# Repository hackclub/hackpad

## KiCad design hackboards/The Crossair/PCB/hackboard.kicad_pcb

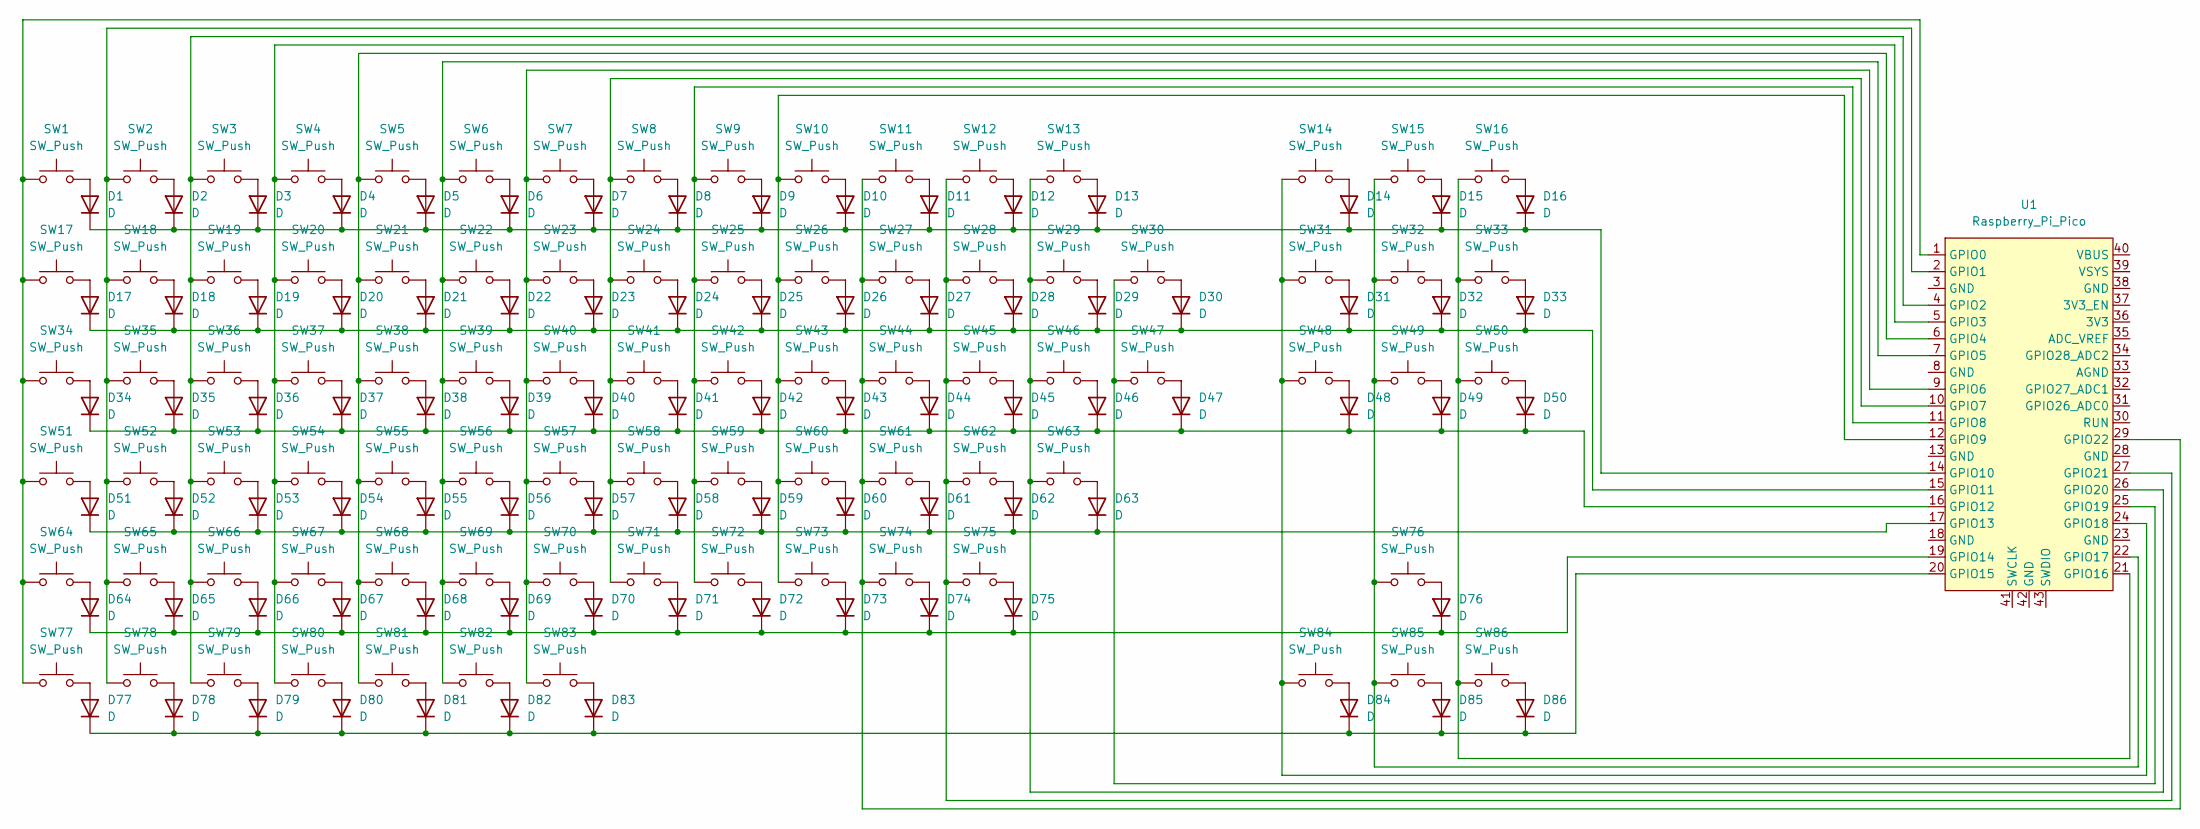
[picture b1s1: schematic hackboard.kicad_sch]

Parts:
D1, D2, D3, D4, D5, D6, D7, D8, D9, D10, D11, D12, D13, D14, D15, D16, D17, D18, D19, D20, D21, D22, D23, D24, D25, D26, D27, D28, D29, D30, D31, D32, D33, D34, D35, D36, D37, D38, D39, D40, D41, D42, D43, D44, D45, D46, D47, D48, D49, D50, D51, D52, D53, D54, D55, D56, D57, D58, D59, D60, D61, D62, D63, D64, D65, D66, D67, D68, D69, D70, D71, D72, D73, D74, D75, D76, D77, D78, D79, D80, D81, D82, D83, D84, D85, D86: D; D_DO-35_SOD27_P7.62mm_Horizontal
SW1, SW2, SW3, SW4, SW5, SW6, SW7, SW8, SW9, SW10, SW11, SW12, SW13, SW14, SW15, SW16, SW17, SW18, SW19, SW20, SW21, SW22, SW23, SW24, SW25, SW26, SW27, SW28, SW29, SW31, SW32, SW33, SW35, SW36, SW37, SW38, SW39, SW40, SW41, SW42, SW43, SW44, SW45, SW46, SW48, SW49, SW50, SW52, SW53, SW54, SW55, SW56, SW57, SW58, SW59, SW60, SW61, SW62, SW65, SW66, SW67, SW68, SW69, SW70, SW71, SW72, SW73, SW74, SW76, SW84, SW85, SW86: SW_Push; SW_Cherry_MX_1.00u_PCB
SW30: SW_Push; SW_Cherry_MX_2.00u_PCB
SW34, SW47, SW77, SW79, SW81, SW82, SW83: SW_Push; SW_Cherry_MX_1.50u_PCB
SW51: SW_Push; SW_Cherry_MX_1.75u_PCB
SW63, SW64: SW_Push; SW_Cherry_MX_2.25u_PCB
SW75: SW_Push; SW_Cherry_MX_2.75u_PCB
SW78: SW_Push; SW_Cherry_MX_1.25u_PCB
SW80: SW_Push; SW_Cherry_MX_6.25u_PCB
U1: Raspberry_Pi_Pico

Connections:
unnamed: D1.2 (A), SW1.2
unnamed: D1.1 (K), D2.1 (K), D3.1 (K), D4.1 (K), D5.1 (K), D6.1 (K), D7.1 (K), D8.1 (K), D9.1 (K), D10.1 (K), D11.1 (K), D12.1 (K), D13.1 (K), D14.1 (K), D15.1 (K), D16.1 (K), U1.14 (GPIO10)
unnamed: D2.2 (A), SW2.2
unnamed: D3.2 (A), SW3.2
unnamed: D4.2 (A), SW4.2
unnamed: D5.2 (A), SW5.2
unnamed: D6.2 (A), SW6.2
unnamed: D7.2 (A), SW7.2
unnamed: D8.2 (A), SW8.2
unnamed: D9.2 (A), SW9.2
unnamed: D10.2 (A), SW10.2
unnamed: D11.2 (A), SW11.2
unnamed: D12.2 (A), SW12.2
unnamed: D13.2 (A), SW13.2
unnamed: D14.2 (A), SW14.2
unnamed: D15.2 (A), SW15.2
unnamed: D16.2 (A), SW16.2
unnamed: D17.2 (A), SW17.2
unnamed: D17.1 (K), D18.1 (K), D19.1 (K), D20.1 (K), D21.1 (K), D22.1 (K), D23.1 (K), D24.1 (K), D25.1 (K), D26.1 (K), D27.1 (K), D28.1 (K), D29.1 (K), D30.1 (K), D31.1 (K), D32.1 (K), D33.1 (K), U1.15 (GPIO11)
unnamed: D18.2 (A), SW18.2
unnamed: D19.2 (A), SW19.2
unnamed: D20.2 (A), SW20.2
unnamed: D21.2 (A), SW21.2
unnamed: D22.2 (A), SW22.2
unnamed: D23.2 (A), SW23.2
unnamed: D24.2 (A), SW24.2
unnamed: D25.2 (A), SW25.2
unnamed: D26.2 (A), SW26.2
unnamed: D27.2 (A), SW27.2
unnamed: D28.2 (A), SW28.2
unnamed: D29.2 (A), SW29.2
unnamed: D30.2 (A), SW30.2
unnamed: D31.2 (A), SW31.2
unnamed: D32.2 (A), SW32.2
unnamed: D33.2 (A), SW33.2
unnamed: D34.2 (A), SW34.2
unnamed: D34.1 (K), D35.1 (K), D36.1 (K), D37.1 (K), D38.1 (K), D39.1 (K), D40.1 (K), D41.1 (K), D42.1 (K), D43.1 (K), D44.1 (K), D45.1 (K), D46.1 (K), D47.1 (K), D48.1 (K), D49.1 (K), D50.1 (K), U1.16 (GPIO12)
unnamed: D35.2 (A), SW35.2
unnamed: D36.2 (A), SW36.2
unnamed: D37.2 (A), SW37.2
unnamed: D38.2 (A), SW38.2
unnamed: D39.2 (A), SW39.2
unnamed: D40.2 (A), SW40.2
unnamed: D41.2 (A), SW41.2
unnamed: D42.2 (A), SW42.2
unnamed: D43.2 (A), SW43.2
unnamed: D44.2 (A), SW44.2
unnamed: D45.2 (A), SW45.2
unnamed: D46.2 (A), SW46.2
unnamed: D47.2 (A), SW47.2
unnamed: D48.2 (A), SW48.2
unnamed: D49.2 (A), SW49.2
unnamed: D50.2 (A), SW50.2
unnamed: D51.2 (A), SW51.2
unnamed: D51.1 (K), D52.1 (K), D53.1 (K), D54.1 (K), D55.1 (K), D56.1 (K), D57.1 (K), D58.1 (K), D59.1 (K), D60.1 (K), D61.1 (K), D62.1 (K), D63.1 (K), U1.17 (GPIO13)
unnamed: D52.2 (A), SW52.2
unnamed: D53.2 (A), SW53.2
unnamed: D54.2 (A), SW54.2
unnamed: D55.2 (A), SW55.2
unnamed: D56.2 (A), SW56.2
unnamed: D57.2 (A), SW57.2
unnamed: D58.2 (A), SW58.2
unnamed: D59.2 (A), SW59.2
unnamed: D60.2 (A), SW60.2
unnamed: D61.2 (A), SW61.2
unnamed: D62.2 (A), SW62.2
unnamed: D63.2 (A), SW63.2
unnamed: D64.2 (A), SW64.2
unnamed: D64.1 (K), D65.1 (K), D66.1 (K), D67.1 (K), D68.1 (K), D69.1 (K), D70.1 (K), D71.1 (K), D72.1 (K), D73.1 (K), D74.1 (K), D75.1 (K), D76.1 (K), U1.19 (GPIO14)
unnamed: D65.2 (A), SW65.2
unnamed: D66.2 (A), SW66.2
unnamed: D67.2 (A), SW67.2
unnamed: D68.2 (A), SW68.2
unnamed: D69.2 (A), SW69.2
unnamed: D70.2 (A), SW70.2
unnamed: D71.2 (A), SW71.2
unnamed: D72.2 (A), SW72.2
unnamed: D73.2 (A), SW73.2
unnamed: D74.2 (A), SW74.2
unnamed: D75.2 (A), SW75.2
unnamed: D76.2 (A), SW76.2
unnamed: D77.2 (A), SW77.2
unnamed: D77.1 (K), D78.1 (K), D79.1 (K), D80.1 (K), D81.1 (K), D82.1 (K), D83.1 (K), D84.1 (K), D85.1 (K), D86.1 (K), U1.20 (GPIO15)
unnamed: D78.2 (A), SW78.2
unnamed: D79.2 (A), SW79.2
unnamed: D80.2 (A), SW80.2
unnamed: D81.2 (A), SW81.2
unnamed: D82.2 (A), SW82.2
unnamed: D83.2 (A), SW83.2
unnamed: D84.2 (A), SW84.2
unnamed: D85.2 (A), SW85.2
unnamed: D86.2 (A), SW86.2
unnamed: SW1.1, SW17.1, SW34.1, SW51.1, SW64.1, SW77.1, U1.1 (GPIO0)
unnamed: SW2.1, SW18.1, SW35.1, SW52.1, SW65.1, SW78.1, U1.2 (GPIO1)
unnamed: SW3.1, SW19.1, SW36.1, SW53.1, SW66.1, SW79.1, U1.4 (GPIO2)
unnamed: SW4.1, SW20.1, SW37.1, SW54.1, SW67.1, SW80.1, U1.5 (GPIO3)
unnamed: SW5.1, SW21.1, SW38.1, SW55.1, SW68.1, SW81.1, U1.6 (GPIO4)
unnamed: SW6.1, SW22.1, SW39.1, SW56.1, SW69.1, SW82.1, U1.7 (GPIO5)
unnamed: SW7.1, SW23.1, SW40.1, SW57.1, SW70.1, SW83.1, U1.9 (GPIO6)
unnamed: SW8.1, SW24.1, SW41.1, SW58.1, SW71.1, U1.10 (GPIO7)
unnamed: SW9.1, SW25.1, SW42.1, SW59.1, SW72.1, U1.11 (GPIO8)
unnamed: SW10.1, SW26.1, SW43.1, SW60.1, SW73.1, U1.12 (GPIO9)
unnamed: SW16.1, SW33.1, SW50.1, SW86.1, U1.21 (GPIO16)
unnamed: SW15.1, SW32.1, SW49.1, SW76.1, SW85.1, U1.22 (GPIO17)
unnamed: SW14.1, SW31.1, SW48.1, SW84.1, U1.24 (GPIO18)
unnamed: SW30.1, SW47.1, U1.25 (GPIO19)
unnamed: SW13.1, SW29.1, SW46.1, SW63.1, U1.26 (GPIO20)
unnamed: SW12.1, SW28.1, SW45.1, SW62.1, SW75.1, U1.27 (GPIO21)
unnamed: SW11.1, SW27.1, SW44.1, SW61.1, SW74.1, U1.29 (GPIO22)

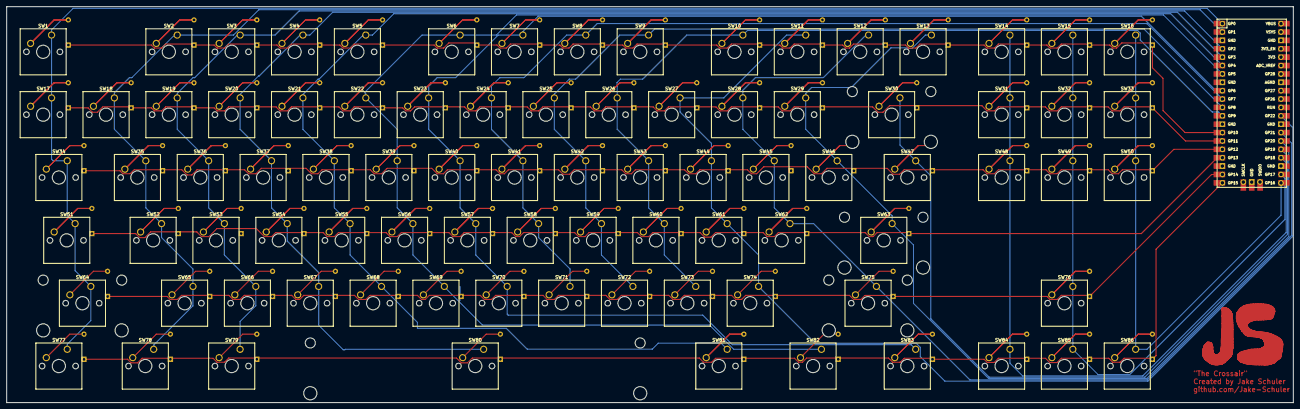
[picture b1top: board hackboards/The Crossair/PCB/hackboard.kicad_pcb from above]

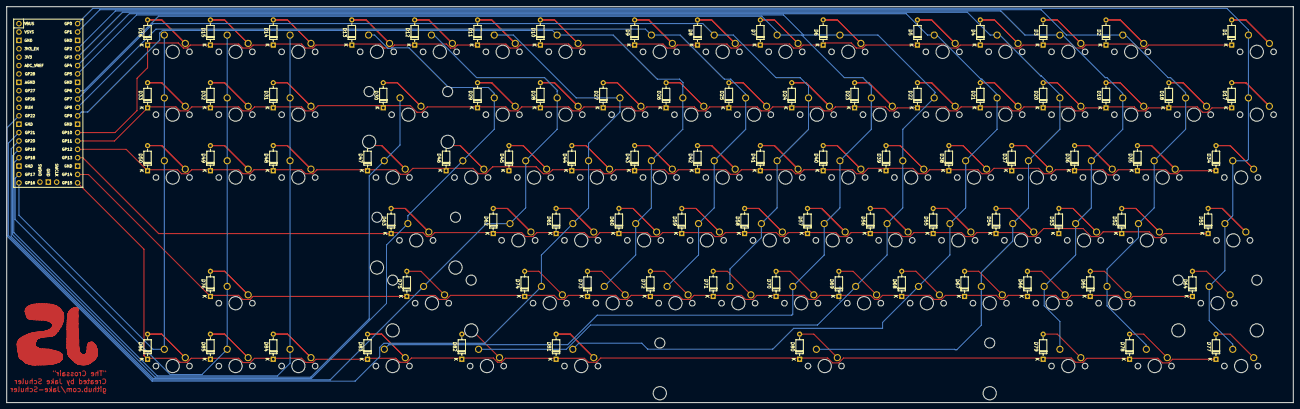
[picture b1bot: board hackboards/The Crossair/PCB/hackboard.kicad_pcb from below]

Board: 2 copper layers, 390.0 x 120.0 mm, 173 parts (86 on the bottom side), 109 nets.

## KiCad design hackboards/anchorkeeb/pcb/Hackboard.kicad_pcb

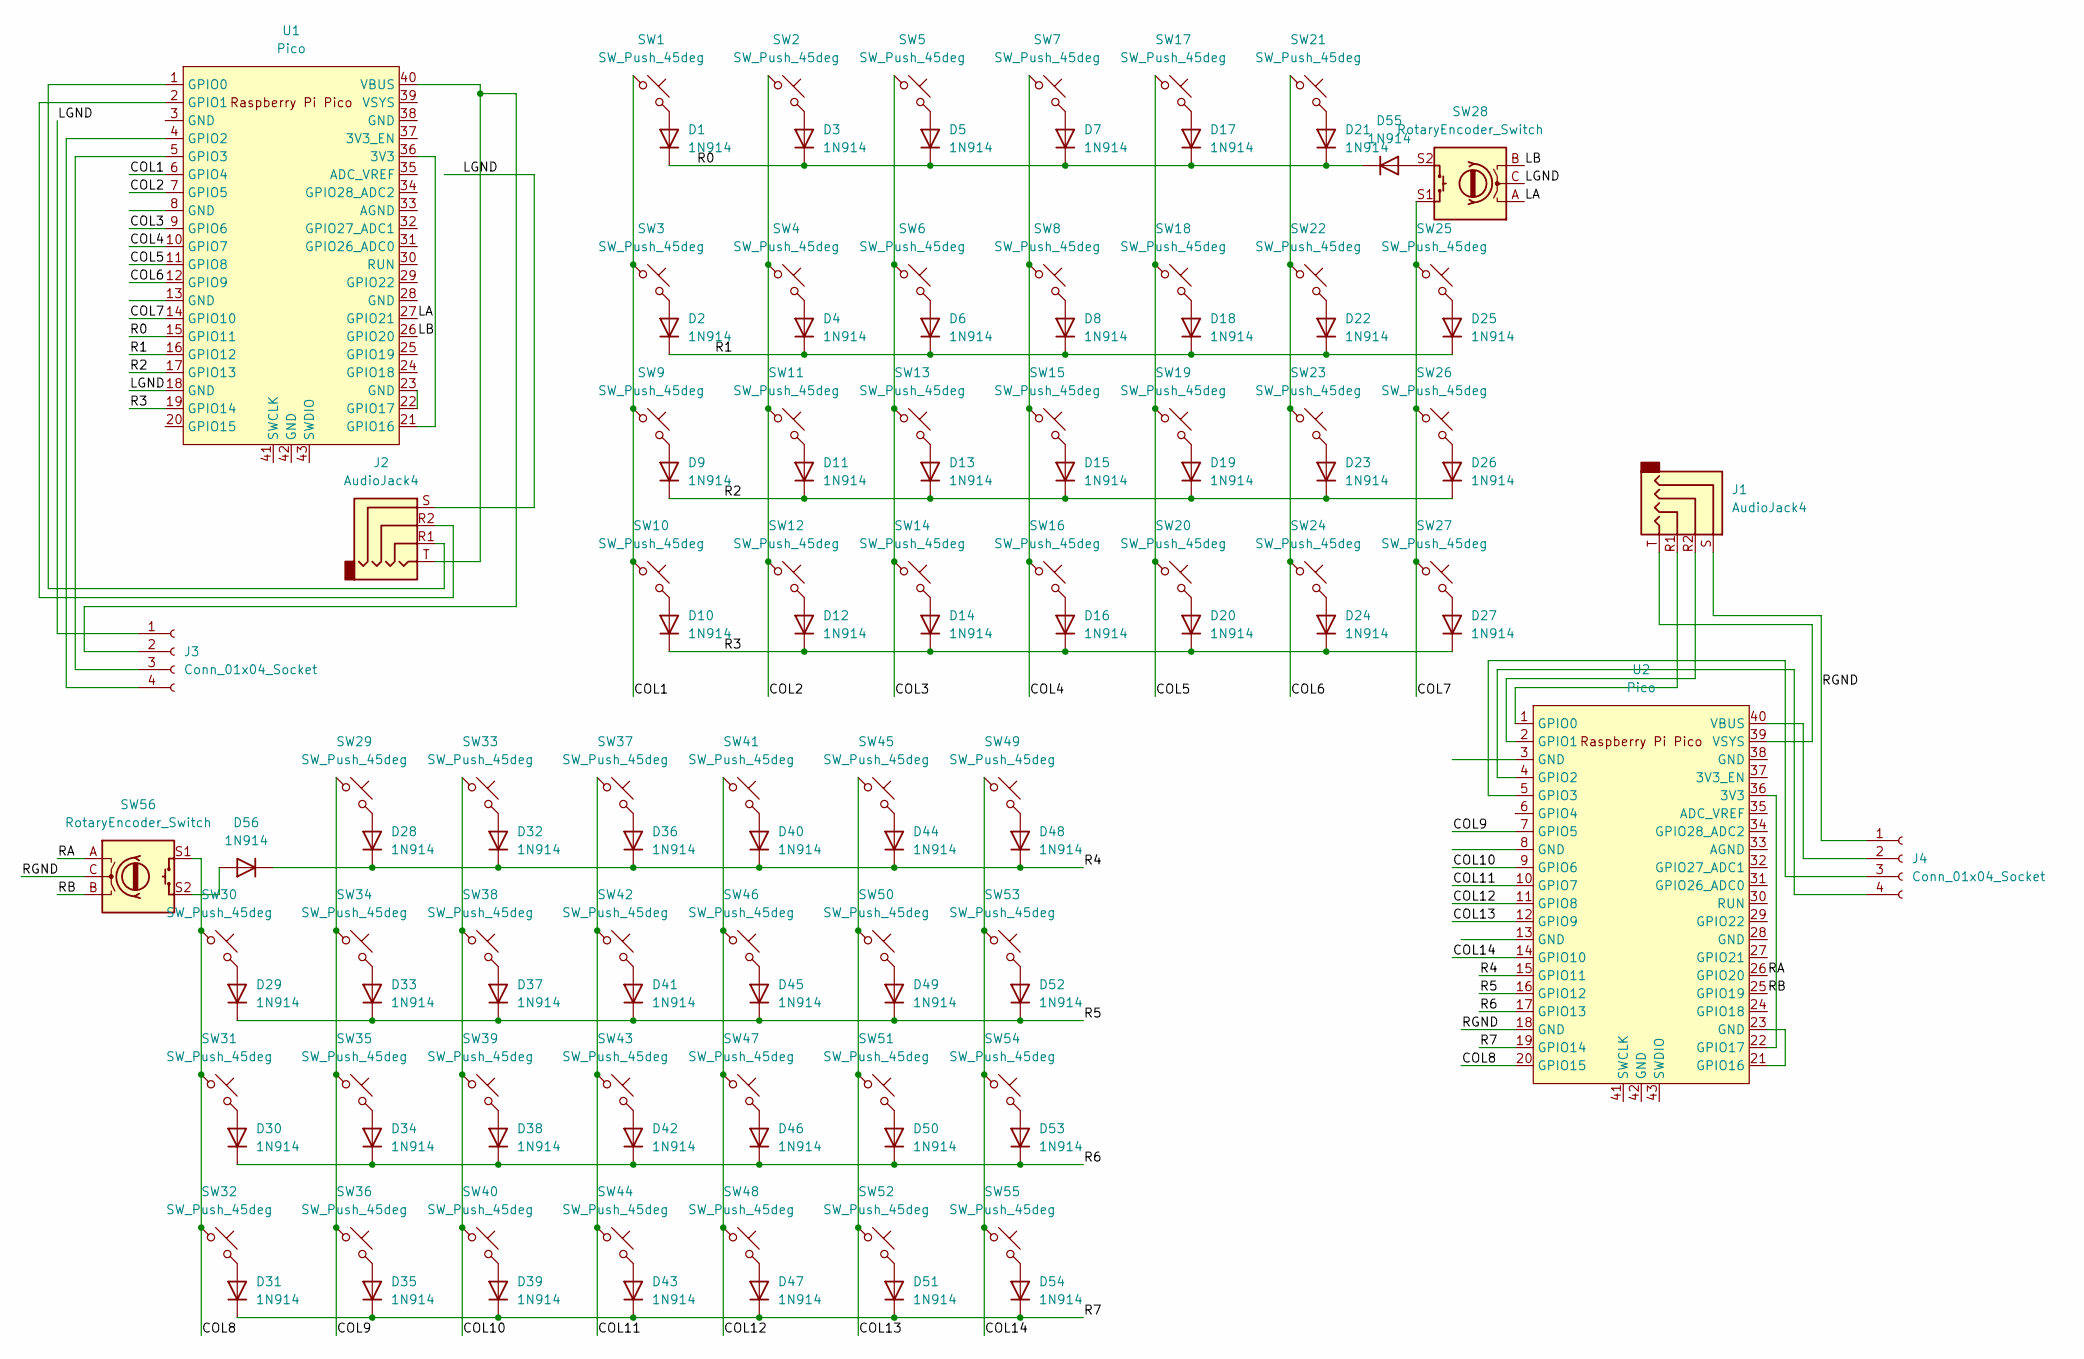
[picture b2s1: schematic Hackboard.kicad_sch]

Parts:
D1, D2, D3, D4, D5, D6, D7, D8, D9, D10, D11, D12, D13, D14, D15, D16, D17, D18, D19, D20, D21, D22, D23, D24, D25, D26, D27, D28, D29, D30, D31, D32, D33, D34, D35, D36, D37, D38, D39, D40, D41, D42, D43, D44, D45, D46, D47, D48, D49, D50, D51, D52, D53, D54, D55, D56: 1N914; D_DO-35_SOD27_P7.62mm_Horizontal
J1, J2: AudioJack4; Jack_3.5mm_PJ320D_Horizontal
J3, J4: Conn_01x04_Socket; SSD1306-0.91-OLED-4pin-128x32
SW1, SW2, SW3, SW4, SW5, SW6, SW7, SW8, SW9, SW10, SW11, SW12, SW13, SW14, SW15, SW16, SW17, SW18, SW19, SW20, SW21, SW22, SW23, SW24, SW25, SW26, SW27, SW29, SW30, SW31, SW32, SW33, SW34, SW35, SW36, SW37, SW38, SW39, SW40, SW41, SW42, SW43, SW44, SW45, SW46, SW47, SW48, SW49, SW50, SW51, SW52, SW53, SW54, SW55: SW_Push_45deg; SW_Cherry_MX_1.00u_PCB
SW28, SW56: RotaryEncoder_Switch; RotaryEncoder_Alps_EC11E-Switch_Vertical_H20mm
U1, U2: Pico; RPi_Pico_SMD_TH

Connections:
/COL1: SW1.1, SW3.1, SW9.1, SW10.1, U1.6 (GPIO4)
/COL2: SW2.1, SW4.1, SW11.1, SW12.1, U1.7 (GPIO5)
/COL3: SW5.1, SW6.1, SW13.1, SW14.1, U1.9 (GPIO6)
/COL4: SW7.1, SW8.1, SW15.1, SW16.1, U1.10 (GPIO7)
/COL5: SW17.1, SW18.1, SW19.1, SW20.1, U1.11 (GPIO8)
/COL6: SW21.1, SW22.1, SW23.1, SW24.1, U1.12 (GPIO9)
/COL7: SW25.1, SW26.1, SW27.1, SW28.S1, U1.14 (GPIO10)
/COL8: SW30.1, SW31.1, SW32.1, SW56.S1, U2.20 (GPIO15)
/COL9: SW29.1, SW34.1, SW35.1, SW36.1, U2.7 (GPIO5)
/COL10: SW33.1, SW38.1, SW39.1, SW40.1, U2.9 (GPIO6)
/COL11: SW37.1, SW42.1, SW43.1, SW44.1, U2.10 (GPIO7)
/COL12: SW41.1, SW46.1, SW47.1, SW48.1, U2.11 (GPIO8)
/COL13: SW45.1, SW50.1, SW51.1, SW52.1, U2.12 (GPIO9)
/COL14: SW49.1, SW53.1, SW54.1, SW55.1, U2.14 (GPIO10)
/LA: SW28.A, U1.27 (GPIO21)
/LB: SW28.B, U1.26 (GPIO20)
/LGND: J2.S, J3.1, SW28.C, U1.18 (GND)
/R0: D1.1 (K), D3.1 (K), D5.1 (K), D7.1 (K), D17.1 (K), D21.1 (K), D55.1 (K), U1.15 (GPIO11)
/R1: D2.1 (K), D4.1 (K), D6.1 (K), D8.1 (K), D18.1 (K), D22.1 (K), D25.1 (K), U1.16 (GPIO12)
/R2: D9.1 (K), D11.1 (K), D13.1 (K), D15.1 (K), D19.1 (K), D23.1 (K), D26.1 (K), U1.17 (GPIO13)
/R3: D10.1 (K), D12.1 (K), D14.1 (K), D16.1 (K), D20.1 (K), D24.1 (K), D27.1 (K), U1.19 (GPIO14)
/R4: D28.1 (K), D32.1 (K), D36.1 (K), D40.1 (K), D44.1 (K), D48.1 (K), D56.1 (K), U2.15 (GPIO11)
/R5: D29.1 (K), D33.1 (K), D37.1 (K), D41.1 (K), D45.1 (K), D49.1 (K), D52.1 (K), U2.16 (GPIO12)
/R6: D30.1 (K), D34.1 (K), D38.1 (K), D42.1 (K), D46.1 (K), D50.1 (K), D53.1 (K), U2.17 (GPIO13)
/R7: D31.1 (K), D35.1 (K), D39.1 (K), D43.1 (K), D47.1 (K), D51.1 (K), D54.1 (K), U2.19 (GPIO14)
/RA: SW56.A, U2.26 (GPIO20)
/RB: SW56.B, U2.25 (GPIO19)
/RGND: J1.S, J4.1, SW56.C, U2.18 (GND)
unnamed: D1.2 (A), SW1.2
unnamed: D2.2 (A), SW3.2
unnamed: D3.2 (A), SW2.2
unnamed: D4.2 (A), SW4.2
unnamed: D5.2 (A), SW5.2
unnamed: D6.2 (A), SW6.2
unnamed: D7.2 (A), SW7.2
unnamed: D8.2 (A), SW8.2
unnamed: D9.2 (A), SW9.2
unnamed: D10.2 (A), SW10.2
unnamed: D11.2 (A), SW11.2
unnamed: D12.2 (A), SW12.2
unnamed: D13.2 (A), SW13.2
unnamed: D14.2 (A), SW14.2
unnamed: D15.2 (A), SW15.2
unnamed: D16.2 (A), SW16.2
unnamed: D17.2 (A), SW17.2
unnamed: D18.2 (A), SW18.2
unnamed: D19.2 (A), SW19.2
unnamed: D20.2 (A), SW20.2
unnamed: D21.2 (A), SW21.2
unnamed: D22.2 (A), SW22.2
unnamed: D23.2 (A), SW23.2
unnamed: D24.2 (A), SW24.2
unnamed: D25.2 (A), SW25.2
unnamed: D26.2 (A), SW26.2
unnamed: D27.2 (A), SW27.2
unnamed: D28.2 (A), SW29.2
unnamed: D29.2 (A), SW30.2
unnamed: D30.2 (A), SW31.2
unnamed: D31.2 (A), SW32.2
unnamed: D32.2 (A), SW33.2
unnamed: D33.2 (A), SW34.2
unnamed: D34.2 (A), SW35.2
unnamed: D35.2 (A), SW36.2
unnamed: D36.2 (A), SW37.2
unnamed: D37.2 (A), SW38.2
unnamed: D38.2 (A), SW39.2
unnamed: D39.2 (A), SW40.2
unnamed: D40.2 (A), SW41.2
unnamed: D41.2 (A), SW42.2
unnamed: D42.2 (A), SW43.2
unnamed: D43.2 (A), SW44.2
unnamed: D44.2 (A), SW45.2
unnamed: D45.2 (A), SW46.2
unnamed: D46.2 (A), SW47.2
unnamed: D47.2 (A), SW48.2
unnamed: D48.2 (A), SW49.2
unnamed: D49.2 (A), SW50.2
unnamed: D50.2 (A), SW51.2
unnamed: D51.2 (A), SW52.2
unnamed: D52.2 (A), SW53.2
unnamed: D53.2 (A), SW54.2
unnamed: D54.2 (A), SW55.2
unnamed: D55.2 (A), SW28.S2
unnamed: D56.2 (A), SW56.S2
unnamed: J2.T, J3.2, U1.40 (VBUS)
unnamed: J3.3, U1.5 (GPIO3)
unnamed: J3.4, U1.4 (GPIO2)
unnamed: J4.2, U2.40 (VBUS)
unnamed: J4.3, U2.5 (GPIO3)
unnamed: J4.4, U2.4 (GPIO2)
unnamed: U1.21 (GPIO16), U1.36 (3V3)
unnamed: J2.R1, U1.1 (GPIO0)
unnamed: J2.R2, U1.2 (GPIO1)
unnamed: U1.22 (GPIO17), U1.23 (GND)
unnamed: U2.22 (GPIO17), U2.36 (3V3)
unnamed: J1.R1, U2.1 (GPIO0)
unnamed: J1.R2, U2.2 (GPIO1)
unnamed: U2.21 (GPIO16), U2.23 (GND)
unnamed: J1.T, U2.39 (VSYS)

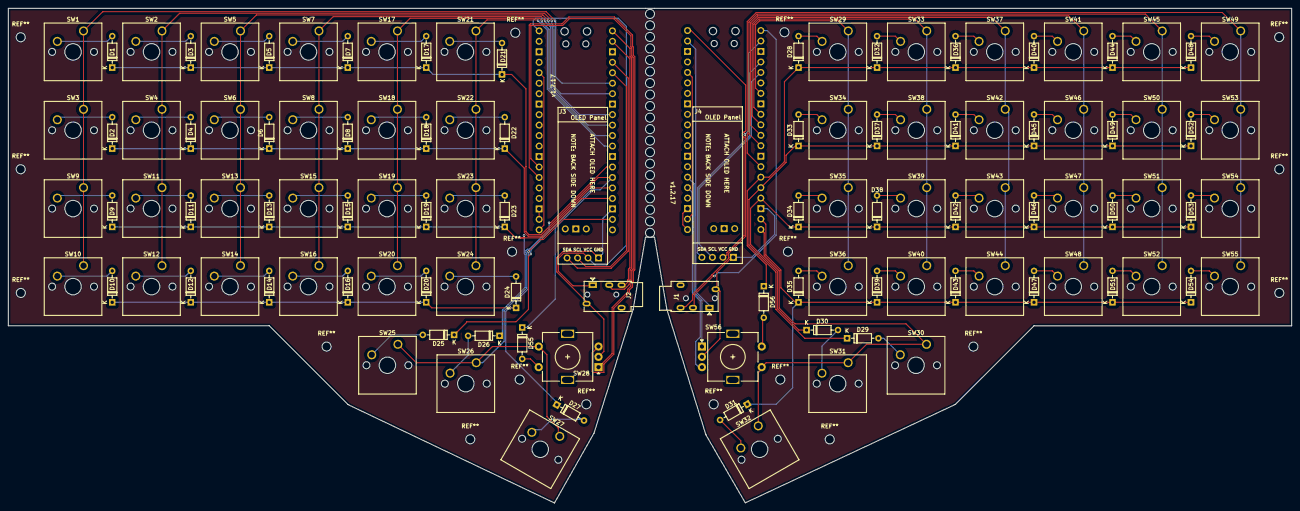
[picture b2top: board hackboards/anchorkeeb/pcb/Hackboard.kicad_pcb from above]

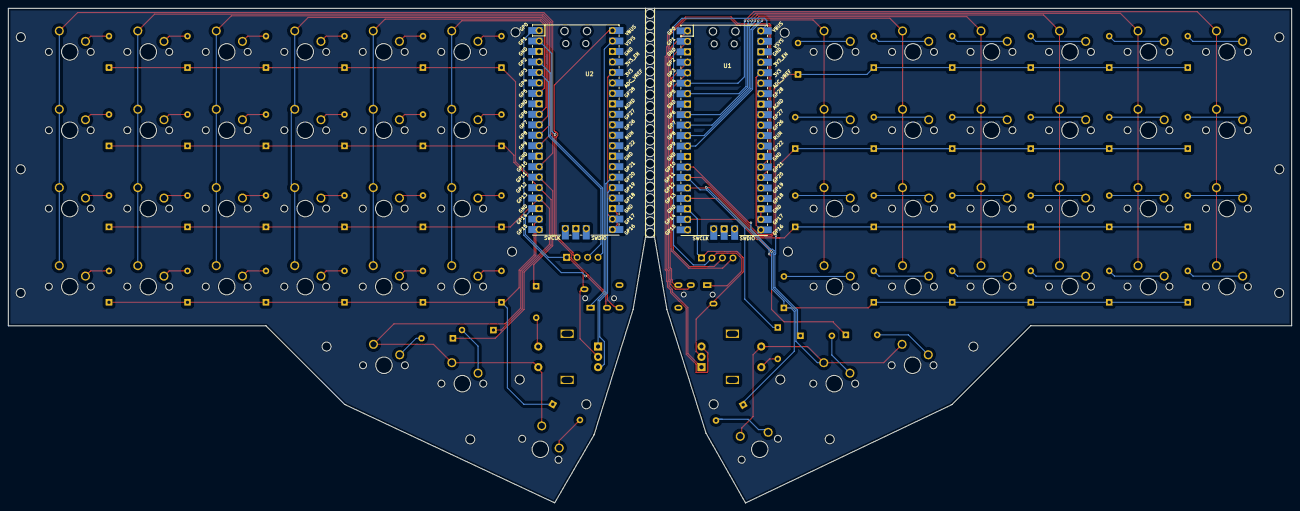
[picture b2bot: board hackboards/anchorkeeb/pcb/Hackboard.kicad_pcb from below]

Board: 2 copper layers, 311.2 x 119.9 mm, 118 parts (2 on the bottom side), 99 nets.

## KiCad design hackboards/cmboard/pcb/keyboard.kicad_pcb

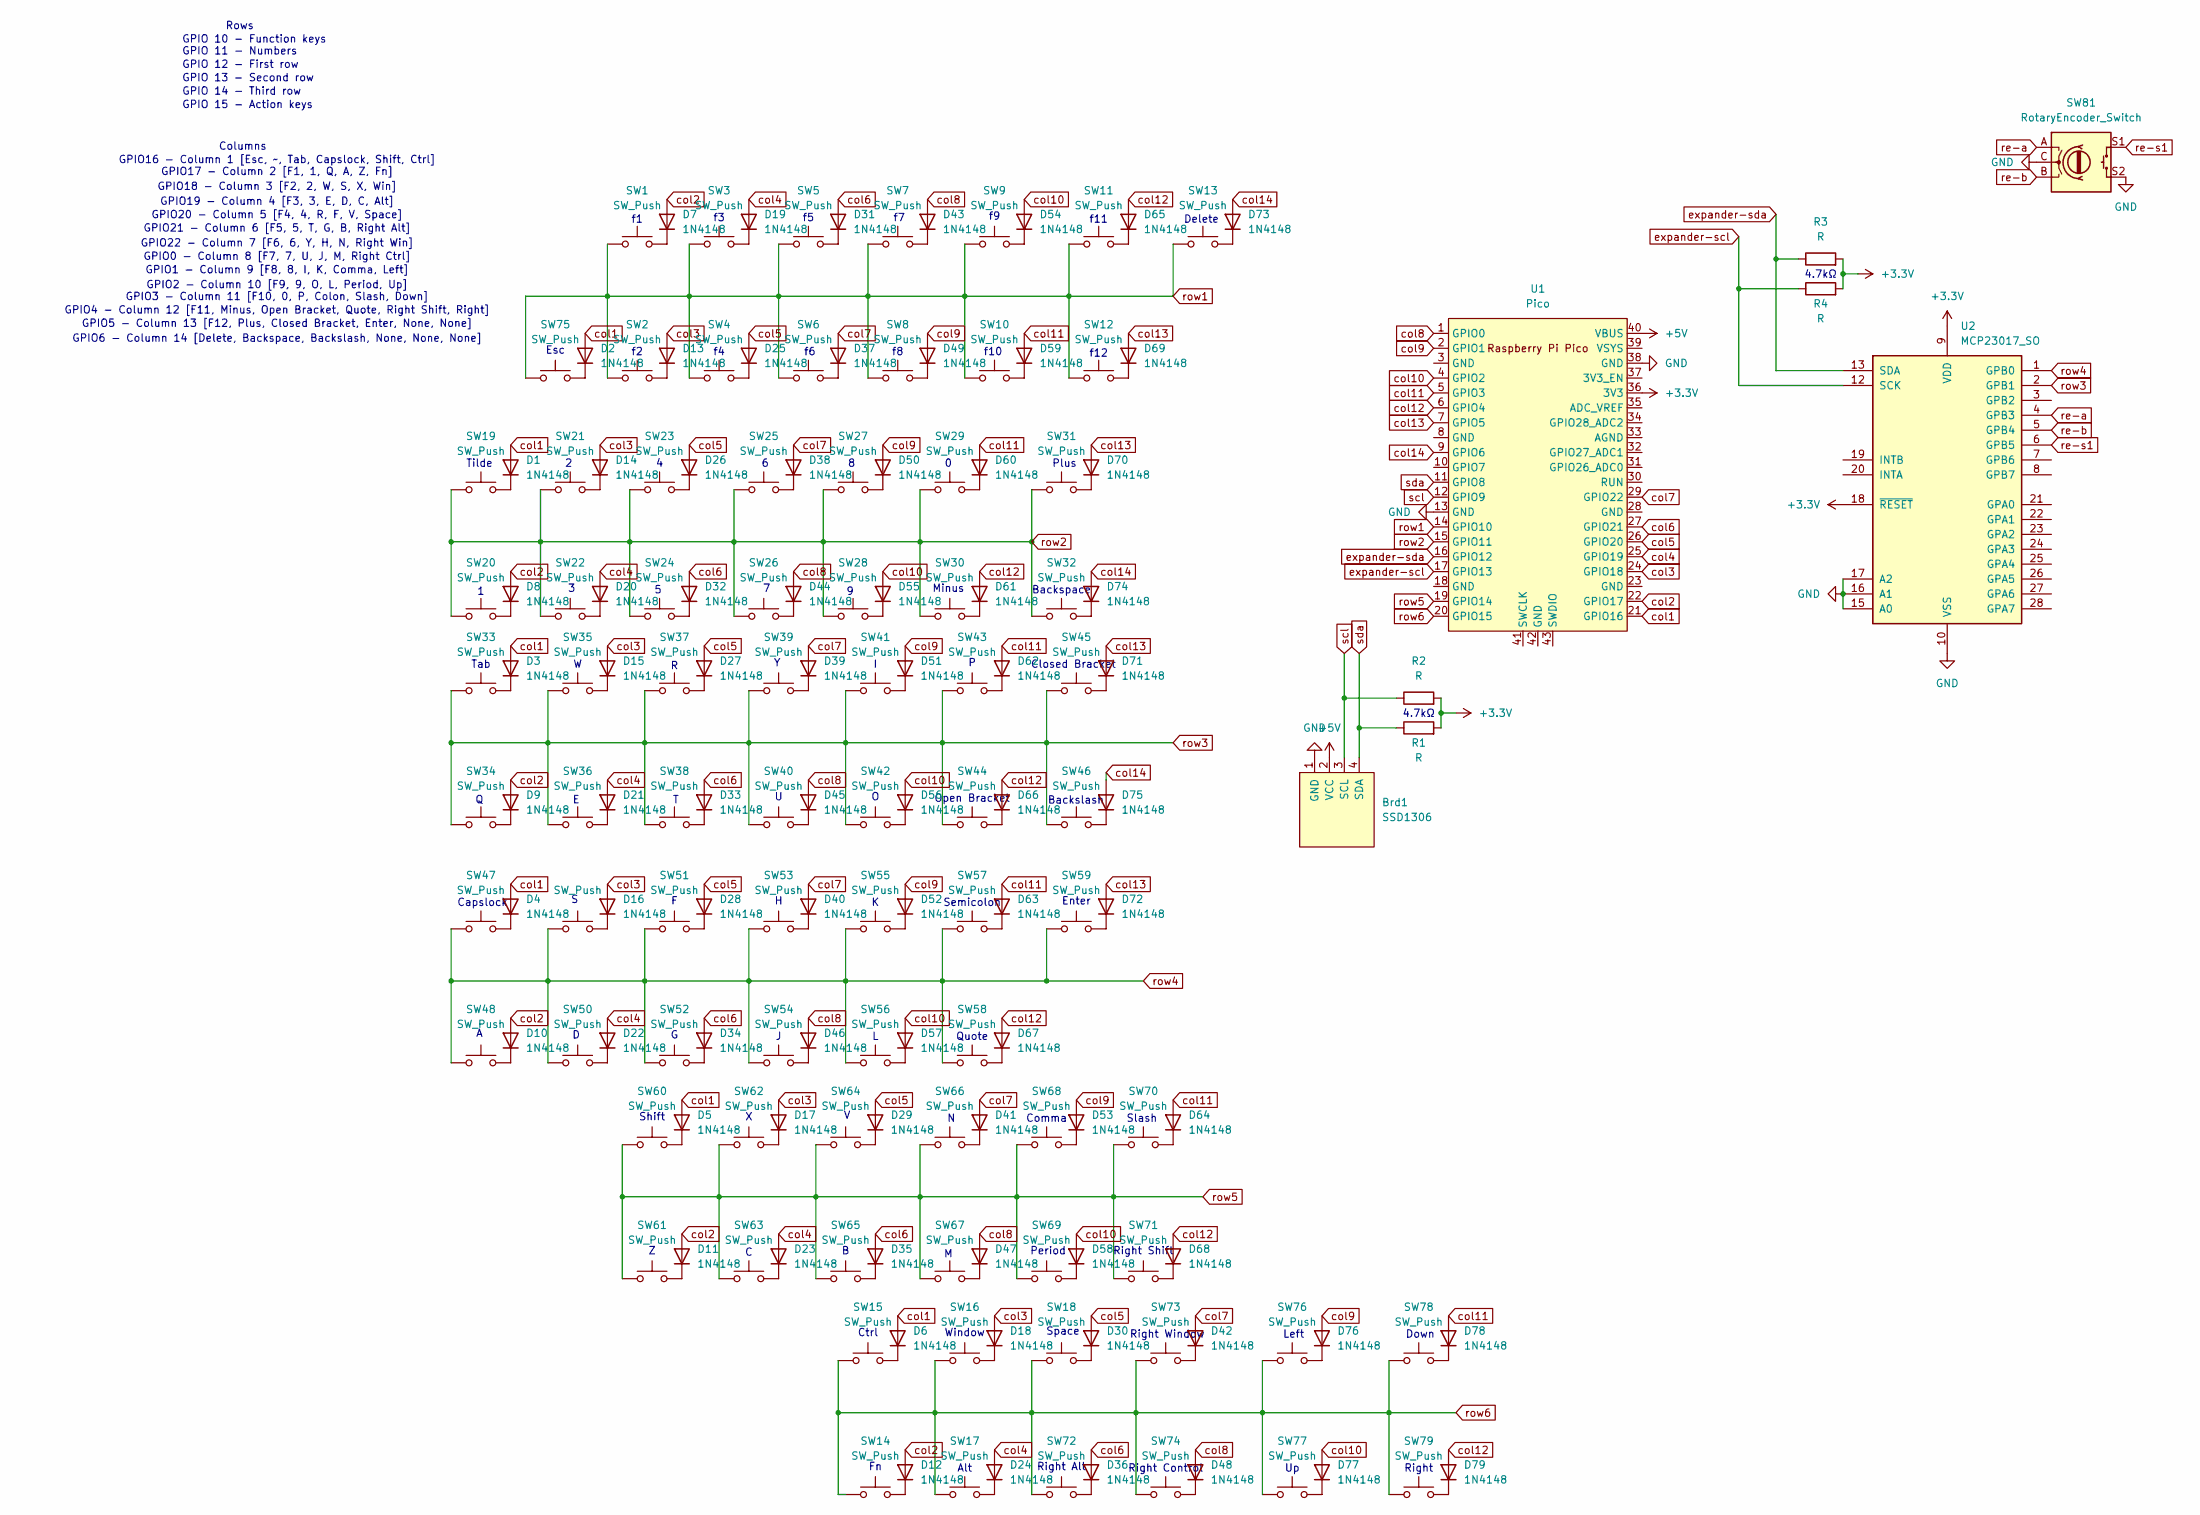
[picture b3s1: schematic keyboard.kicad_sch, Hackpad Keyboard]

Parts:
Brd1: SSD1306; 128x64OLED
D1, D2, D3, D4, D5, D6, D7, D8, D9, D10, D11, D12, D13, D14, D15, D16, D17, D18, D19, D20, D21, D22, D23, D24, D25, D26, D27, D28, D29, D30, D31, D32, D33, D34, D35, D36, D37, D38, D39, D40, D41, D42, D43, D44, D45, D46, D47, D48, D49, D50, D51, D52, D53, D54, D55, D56, D57, D58, D59, D60, D61, D62, D63, D64, D65, D66, D67, D68, D69, D70, D71, D72, D73, D74, D75, D76, D77, D78, D79: 1N4148; D_DO-35_SOD27_P7.62mm_Horizontal
R1, R2, R3, R4: R; R_Axial_DIN0204_L3.6mm_D1.6mm_P7.62mm_Horizontal
SW1, SW2, SW3, SW4, SW5, SW6, SW7, SW8, SW9, SW10, SW11, SW12, SW14, SW16, SW17, SW19, SW20, SW21, SW22, SW23, SW24, SW25, SW26, SW27, SW28, SW29, SW30, SW31, SW34, SW35, SW36, SW37, SW38, SW39, SW40, SW41, SW42, SW43, SW44, SW45, SW48, SW49, SW50, SW51, SW52, SW53, SW54, SW55, SW56, SW57, SW58, SW61, SW62, SW63, SW64, SW65, SW66, SW67, SW68, SW69, SW70, SW72, SW76, SW77, SW78, SW79: SW_Push; SW_Cherry_MX_1.00u_PCB
SW13, SW15, SW75: SW_Push; SW_Cherry_MX_1.50u_PCB
SW18: SW_Push; SW_Cherry_MX_6.25u_PCB
SW32, SW74: SW_Push; SW_Cherry_MX_2.00u_PCB
SW33: SW_Push; SW_Cherry_MX_1.75u_PCB
SW46, SW73: SW_Push; SW_Cherry_MX_1.25u_PCB
SW47: SW_Push; SW_Cherry_MX_1.75u_Plate
SW59, SW60: SW_Push; SW_Cherry_MX_2.25u_PCB
SW71: SW_Push; SW_Cherry_MX_2.75u_PCB
SW81: RotaryEncoder_Switch; RotaryEncoder_Alps_EC11E-Switch_Vertical_H20mm_CircularMoun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
U1: Pico; RPi_Pico_SMD_TH
U2: MCP23017_SO; SOIC-28W_7.5x17.9mm_P1.27mm

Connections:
+3.3V: R1.2, R2.2, R3.2, R4.2, U1.36 (3V3), U2.9 (VDD), U2.18 (~RESET)
+5V: Brd1.2 (VCC), U1.40 (VBUS)
GND: Brd1.1 (GND), SW81.C, SW81.S2, U1.13 (GND), U1.38 (GND), U2.10 (VSS), U2.15 (A0), U2.16 (A1), U2.17 (A2)
unnamed: D1.1 (K), SW19.2
unnamed: D2.1 (K), SW75.2
unnamed: D3.1 (K), SW33.2
unnamed: D4.1 (K), SW47.2
unnamed: D5.1 (K), SW60.2
unnamed: D6.1 (K), SW15.2
unnamed: D7.1 (K), SW1.2
unnamed: D8.1 (K), SW20.2
unnamed: D9.1 (K), SW34.2
unnamed: D10.1 (K), SW48.2
unnamed: D11.1 (K), SW61.2
unnamed: D12.1 (K), SW14.2
unnamed: D13.1 (K), SW2.2
unnamed: D14.1 (K), SW21.2
unnamed: D15.1 (K), SW35.2
unnamed: D16.1 (K), SW49.2
unnamed: D17.1 (K), SW62.2
unnamed: D18.1 (K), SW16.2
unnamed: D19.1 (K), SW3.2
unnamed: D20.1 (K), SW22.2
unnamed: D21.1 (K), SW36.2
unnamed: D22.1 (K), SW50.2
unnamed: D23.1 (K), SW63.2
unnamed: D24.1 (K), SW17.2
unnamed: D25.1 (K), SW4.2
unnamed: D26.1 (K), SW23.2
unnamed: D27.1 (K), SW37.2
unnamed: D28.1 (K), SW51.2
unnamed: D29.1 (K), SW64.2
unnamed: D30.1 (K), SW18.2
unnamed: D31.1 (K), SW5.2
unnamed: D32.1 (K), SW24.2
unnamed: D33.1 (K), SW38.2
unnamed: D34.1 (K), SW52.2
unnamed: D35.1 (K), SW65.2
unnamed: D36.1 (K), SW72.2
unnamed: D37.1 (K), SW6.2
unnamed: D38.1 (K), SW25.2
unnamed: D39.1 (K), SW39.2
unnamed: D40.1 (K), SW53.2
unnamed: D41.1 (K), SW66.2
unnamed: D42.1 (K), SW73.2
unnamed: D43.1 (K), SW7.2
unnamed: D44.1 (K), SW26.2
unnamed: D45.1 (K), SW40.2
unnamed: D46.1 (K), SW54.2
unnamed: D47.1 (K), SW67.2
unnamed: D48.1 (K), SW74.2
unnamed: D49.1 (K), SW8.2
unnamed: D50.1 (K), SW27.2
unnamed: D51.1 (K), SW41.2
unnamed: D52.1 (K), SW55.2
unnamed: D53.1 (K), SW68.2
unnamed: D54.1 (K), SW9.2
unnamed: D55.1 (K), SW28.2
unnamed: D56.1 (K), SW42.2
unnamed: D57.1 (K), SW56.2
unnamed: D58.1 (K), SW69.2
unnamed: D59.1 (K), SW10.2
unnamed: D60.1 (K), SW29.2
unnamed: D61.1 (K), SW30.2
unnamed: D62.1 (K), SW43.2
unnamed: D63.1 (K), SW57.2
unnamed: D64.1 (K), SW70.2
unnamed: D65.1 (K), SW11.2
unnamed: D66.1 (K), SW44.2
unnamed: D67.1 (K), SW58.2
unnamed: D68.1 (K), SW71.2
unnamed: D69.1 (K), SW12.2
unnamed: D70.1 (K), SW31.2
unnamed: D71.1 (K), SW45.2
unnamed: D72.1 (K), SW59.2
unnamed: D73.1 (K), SW13.2
unnamed: D74.1 (K), SW32.2
unnamed: D75.1 (K), SW46.2
unnamed: D76.1 (K), SW76.2
unnamed: D77.1 (K), SW77.2
unnamed: D78.1 (K), SW78.2
unnamed: D79.1 (K), SW79.2
col1: D1.2 (A), D2.2 (A), D3.2 (A), D4.2 (A), D5.2 (A), D6.2 (A), U1.21 (GPIO16)
col2: D7.2 (A), D8.2 (A), D9.2 (A), D10.2 (A), D11.2 (A), D12.2 (A), U1.22 (GPIO17)
col3: D13.2 (A), D14.2 (A), D15.2 (A), D16.2 (A), D17.2 (A), D18.2 (A), U1.24 (GPIO18)
col4: D19.2 (A), D20.2 (A), D21.2 (A), D22.2 (A), D23.2 (A), D24.2 (A), U1.25 (GPIO19)
col5: D25.2 (A), D26.2 (A), D27.2 (A), D28.2 (A), D29.2 (A), D30.2 (A), U1.26 (GPIO20)
col6: D31.2 (A), D32.2 (A), D33.2 (A), D34.2 (A), D35.2 (A), D36.2 (A), U1.27 (GPIO21)
col7: D37.2 (A), D38.2 (A), D39.2 (A), D40.2 (A), D41.2 (A), D42.2 (A), U1.29 (GPIO22)
col8: D43.2 (A), D44.2 (A), D45.2 (A), D46.2 (A), D47.2 (A), D48.2 (A), U1.1 (GPIO0)
col9: D49.2 (A), D50.2 (A), D51.2 (A), D52.2 (A), D53.2 (A), D76.2 (A), U1.2 (GPIO1)
col10: D54.2 (A), D55.2 (A), D56.2 (A), D57.2 (A), D58.2 (A), D77.2 (A), U1.4 (GPIO2)
col11: D59.2 (A), D60.2 (A), D62.2 (A), D63.2 (A), D64.2 (A), D78.2 (A), U1.5 (GPIO3)
col12: D61.2 (A), D65.2 (A), D66.2 (A), D67.2 (A), D68.2 (A), D79.2 (A), U1.6 (GPIO4)
col13: D69.2 (A), D70.2 (A), D71.2 (A), D72.2 (A), U1.7 (GPIO5)
col14: D73.2 (A), D74.2 (A), D75.2 (A), U1.9 (GPIO6)
expander-scl: R4.1, U1.17 (GPIO13), U2.12 (SCK)
expander-sda: R3.1, U1.16 (GPIO12), U2.13 (SDA)
re-a: SW81.A, U2.4 (GPB3)
re-b: SW81.B, U2.5 (GPB4)
re-s1: SW81.S1, U2.6 (GPB5)
row1: SW1.1, SW2.1, SW3.1, SW4.1, SW5.1, SW6.1, SW7.1, SW8.1, SW9.1, SW10.1, SW11.1, SW12.1, SW13.1, SW75.1, U1.14 (GPIO10)
row2: SW19.1, SW20.1, SW21.1, SW22.1, SW23.1, SW24.1, SW25.1, SW26.1, SW27.1, SW28.1, SW29.1, SW30.1, SW31.1, SW32.1, U1.15 (GPIO11)
row3: SW33.1, SW34.1, SW35.1, SW36.1, SW37.1, SW38.1, SW39.1, SW40.1, SW41.1, SW42.1, SW43.1, SW44.1, SW45.1, SW46.1, U2.2 (GPB1)
row4: SW47.1, SW48.1, SW49.1, SW50.1, SW51.1, SW52.1, SW53.1, SW54.1, SW55.1, SW56.1, SW57.1, SW58.1, SW59.1, U2.1 (GPB0)
row5: SW60.1, SW61.1, SW62.1, SW63.1, SW64.1, SW65.1, SW66.1, SW67.1, SW68.1, SW69.1, SW70.1, SW71.1, U1.19 (GPIO14)
row6: SW14.1, SW15.1, SW16.1, SW17.1, SW18.1, SW72.1, SW73.1, SW74.1, SW76.1, SW77.1, SW78.1, SW79.1, U1.20 (GPIO15)
scl: Brd1.3 (SCL), R2.1, U1.12 (GPIO9)
sda: Brd1.4 (SDA), R1.1, U1.11 (GPIO8)

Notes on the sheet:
f11
Tilde
GPIO6 - Column 14 [Delete, Backspace, Backslash, None, None, None]
Right Control
GPIO0 - Column 8 [F7, 7, U, J, M, Right Ctrl]
4.7kΩ
Right Alt
Columns
GPIO16 - Column 1 [Esc, ~, Tab, Capslock, Shift, Ctrl]
GPIO1 - Column 9 [F8, 8, I, K, Comma, Left]
GPIO 10 - Function keys
f10
GPIO5 - Column 13 [F12, Plus, Closed Bracket, Enter, None, None]
Right Shift
Plus
Tab
GPIO20 - Column 5 [F4, 4, R, F, V, Space]
Semicolon
GPIO 11 - Numbers
GPIO 15 - Action keys
GPIO4 - Column 12 [F11, Minus, Open Bracket, Quote, Right Shift, Right]
Backslash
GPIO 13 - Second row
Comma
GPIO19 - Column 4 [F3, 3, E, D, C, Alt]
Right
Shift
GPIO2 - Column 10 [F9, 9, O, L, Period, Up]
Delete
Left
Window
GPIO17 - Column 2 [F1, 1, Q, A, Z, Fn]
Right Window
Minus
Quote
Down
Slash
f12
GPIO 14 - Third row
Enter

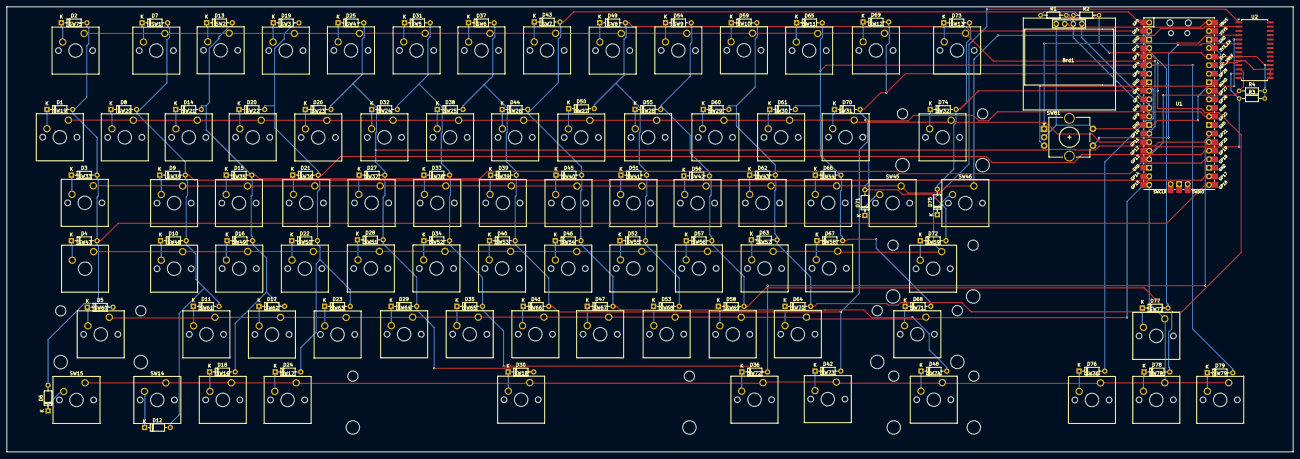
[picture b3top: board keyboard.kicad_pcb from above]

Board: 2 copper layers, 382.2 x 132.2 mm, 166 parts (0 on the bottom side), 109 nets.
